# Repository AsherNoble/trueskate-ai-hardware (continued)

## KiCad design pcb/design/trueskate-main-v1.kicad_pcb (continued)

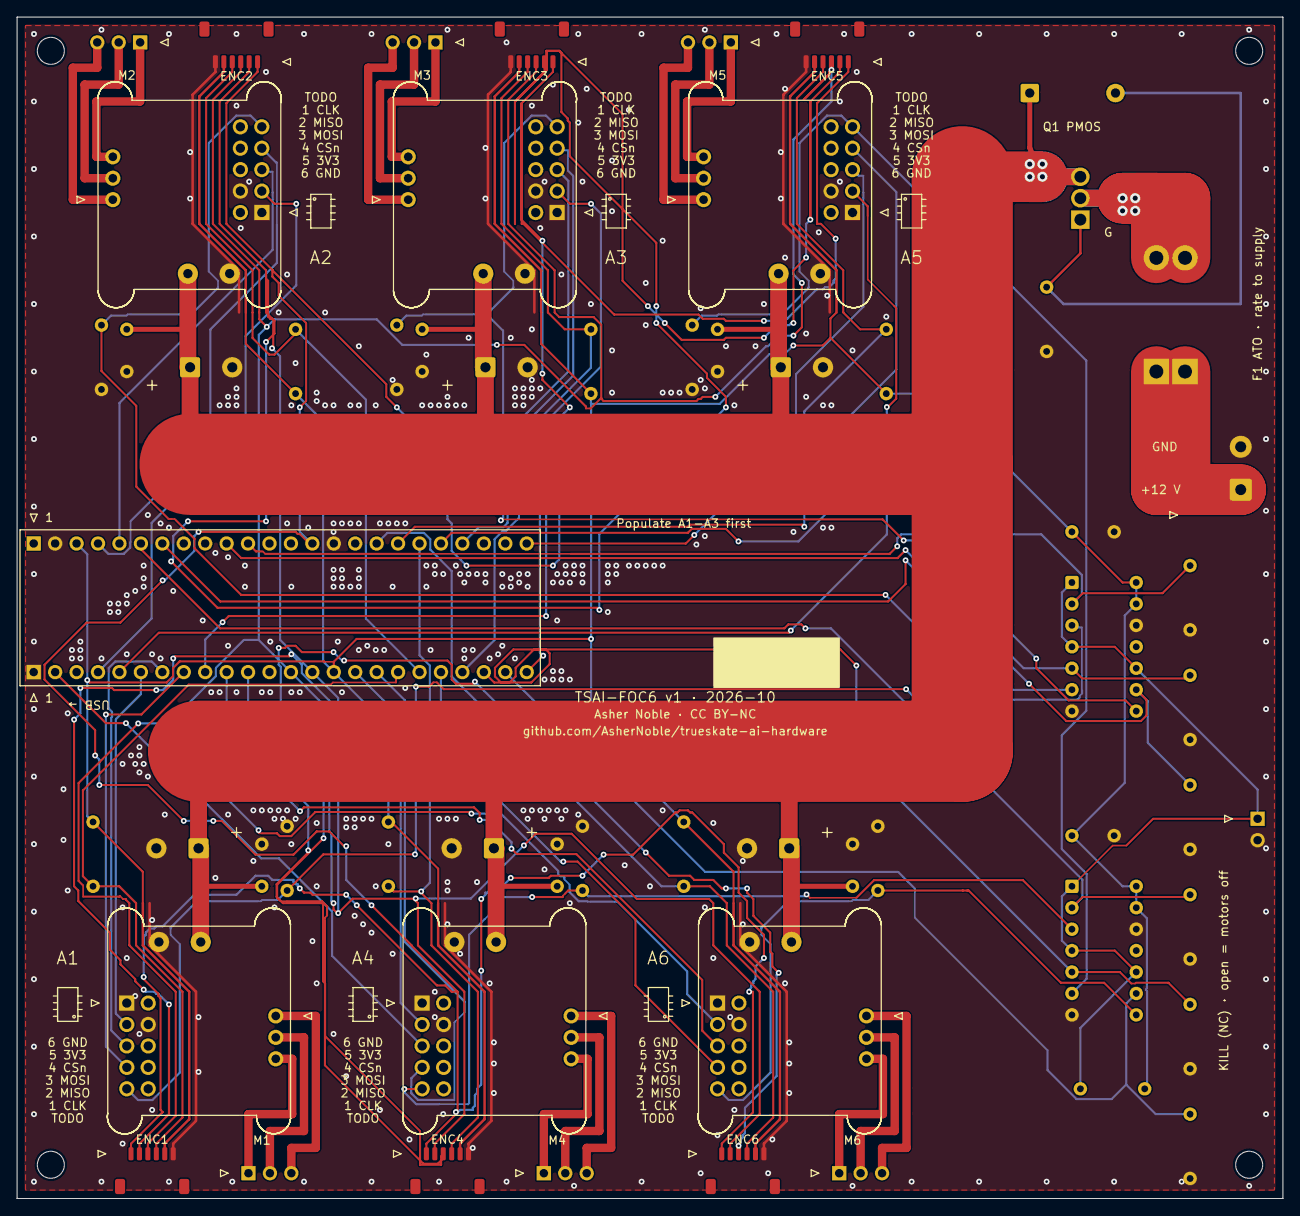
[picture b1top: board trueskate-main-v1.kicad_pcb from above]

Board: 2 copper layers, 150.0 x 140.0 mm, 65 parts (0 on the bottom side), 64 nets.

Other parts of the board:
H1, H2, H3, H4: MountingHole_3.2mm_M3

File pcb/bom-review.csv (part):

Reference,Quantity,Value,Footprint,LCSC,Assembly,Estimated USD each,Notes
J1,1,Teensy 4.1 FEMALE 1x24,TrueSkate:Edge_PinSocket_1x24_P2.54mm_Vertical,,Hand,1.5,"Physical pin legend: GND,0,1,2,3,4,5,6,7,8,9,10,11,12,3V3,24,25,26,27,28,29,30,31,32"
J2,1,Teensy 4.1 FEMALE 1x24,TrueSkate:Edge_PinSocket_1x24_P2.54mm_Vertical,,Hand,1.5,"Physical pin legend: VIN,GND,3V3,23,22,21,20,19,18,17,16,15,14,13,GND,41,40,39,38,37,36,35,34,33"
J11,1,Mini v1.0 / 15-hole socket,TrueSkate:SimpleFOC_Mini_v1.0,,Hand,0.7,Optional axis; female 2x5 + female 1x3 + two >=3A single receptacles; matched mating height
J21,1,MOTOR PHASES male 1x3,TrueSkate:Edge_PinHeader_1x03_P2.54mm_Vertical,,Hand,0.1,Optional axis; outward cable clearance at front edge
J31,1,SM06B-SRSS-TB,TrueSkate:Edge_JST_SH_SM06B-SRSS-TB_1x06-1MP_P1.00mm_Horizontal,C7588156,JLCPCB,0.5,Optional axis; side entry opens toward front (-Y); SH harness pin order UNVERIFIED
R21,1,10k EN pull-down,TrueSkate:Edge_R_Axial_DIN0207_L6.3mm_D2.5mm_P7.62mm_Horizontal,,Hand,0.05,"Optional axis; fit with Mini; 10k, 5% or better"
R31,1,10k CS pull-up,TrueSkate:Edge_R_Axial_DIN0207_L6.3mm_D2.5mm_P7.62mm_Horizontal,,Hand,0.05,"Optional axis; fit with encoder; 10k, 5% or better"
C11,1,1000uF 35V EEUFR1V102B,TrueSkate:Edge_CP_Radial_D12.5mm_P5.00mm,C128476,Hand / owned,0,Optional axis; owned Panasonic diameter12.5mm height20mm pitch5mm
C21,1,100nF 50V ceramic,TrueSkate:Edge_C_Disc_D5.0mm_W2.5mm_P5.00mm,C2979769,Hand,0.13,Optional axis; Vishay K104K10X7RF5UH5
J12,1,Mini v1.0 / 15-hole socket,TrueSkate:SimpleFOC_Mini_v1.0,,Hand,0.7,Optional axis; female 2x5 + female 1x3 + two >=3A single receptacles; matched mating height
J22,1,MOTOR PHASES male 1x3,TrueSkate:Edge_PinHeader_1x03_P2.54mm_Vertical,,Hand,0.1,Optional axis; outward cable clearance at front edge
J32,1,SM06B-SRSS-TB,TrueSkate:Edge_JST_SH_SM06B-SRSS-TB_1x06-1MP_P1.00mm_Horizontal,C7588156,JLCPCB,0.5,Optional axis; side entry opens toward front (-Y); SH harness pin order UNVERIFIED
R22,1,10k EN pull-down,TrueSkate:Edge_R_Axial_DIN0207_L6.3mm_D2.5mm_P7.62mm_Horizontal,,Hand,0.05,"Optional axis; fit with Mini; 10k, 5% or better"
R32,1,10k CS pull-up,TrueSkate:Edge_R_Axial_DIN0207_L6.3mm_D2.5mm_P7.62mm_Horizontal,,Hand,0.05,"Optional axis; fit with encoder; 10k, 5% or better"
C12,1,1000uF 35V EEUFR1V102B,TrueSkate:Edge_CP_Radial_D12.5mm_P5.00mm,C128476,Hand / owned,0,Optional axis; owned Panasonic diameter12.5mm height20mm pitch5mm
C22,1,100nF 50V ceramic,TrueSkate:Edge_C_Disc_D5.0mm_W2.5mm_P5.00mm,C2979769,Hand,0.13,Optional axis; Vishay K104K10X7RF5UH5
J13,1,Mini v1.0 / 15-hole socket,TrueSkate:SimpleFOC_Mini_v1.0,,Hand,0.7,Optional axis; female 2x5 + female 1x3 + two >=3A single receptacles; matched mating height
J23,1,MOTOR PHASES male 1x3,TrueSkate:Edge_PinHeader_1x03_P2.54mm_Vertical,,Hand,0.1,Optional axis; outward cable clearance at front edge
J33,1,SM06B-SRSS-TB,TrueSkate:Edge_JST_SH_SM06B-SRSS-TB_1x06-1MP_P1.00mm_Horizontal,C7588156,JLCPCB,0.5,Optional axis; side entry opens toward front (-Y); SH harness pin order UNVERIFIED
R23,1,10k EN pull-down,TrueSkate:Edge_R_Axial_DIN0207_L6.3mm_D2.5mm_P7.62mm_Horizontal,,Hand,0.05,"Optional axis; fit with Mini; 10k, 5% or better"
R33,1,10k CS pull-up,TrueSkate:Edge_R_Axial_DIN0207_L6.3mm_D2.5mm_P7.62mm_Horizontal,,Hand,0.05,"Optional axis; fit with encoder; 10k, 5% or better"
C13,1,1000uF 35V EEUFR1V102B,TrueSkate:Edge_CP_Radial_D12.5mm_P5.00mm,C128476,Hand / owned,0,Optional axis; owned Panasonic diameter12.5mm height20mm pitch5mm
C23,1,100nF 50V ceramic,TrueSkate:Edge_C_Disc_D5.0mm_W2.5mm_P5.00mm,C2979769,Hand,0.13,Optional axis; Vishay K104K10X7RF5UH5
J14,1,Mini v1.0 / 15-hole socket,TrueSkate:SimpleFOC_Mini_v1.0,,Hand,0.7,Optional axis; female 2x5 + female 1x3 + two >=3A single receptacles; matched mating height
J24,1,MOTOR PHASES male 1x3,TrueSkate:Edge_PinHeader_1x03_P2.54mm_Vertical,,Hand,0.1,Optional axis; outward cable clearance at front edge
J34,1,SM06B-SRSS-TB,TrueSkate:Edge_JST_SH_SM06B-SRSS-TB_1x06-1MP_P1.00mm_Horizontal,C7588156,JLCPCB,0.5,Optional axis; side entry opens toward front (-Y); SH harness pin order UNVERIFIED
R24,1,10k EN pull-down,TrueSkate:Edge_R_Axial_DIN0207_L6.3mm_D2.5mm_P7.62mm_Horizontal,,Hand,0.05,"Optional axis; fit with Mini; 10k, 5% or better"
R34,1,10k CS pull-up,TrueSkate:Edge_R_Axial_DIN0207_L6.3mm_D2.5mm_P7.62mm_Horizontal,,Hand,0.05,"Optional axis; fit with encoder; 10k, 5% or better"
C14,1,1000uF 35V EEUFR1V102B,TrueSkate:Edge_CP_Radial_D12.5mm_P5.00mm,C128476,Hand / owned,0,Optional axis; owned Panasonic diameter12.5mm height20mm pitch5mm
C24,1,100nF 50V ceramic,TrueSkate:Edge_C_Disc_D5.0mm_W2.5mm_P5.00mm,C2979769,Hand,0.13,Optional axis; Vishay K104K10X7RF5UH5
J15,1,Mini v1.0 / 15-hole socket,TrueSkate:SimpleFOC_Mini_v1.0,,Hand,0.7,Optional axis; female 2x5 + female 1x3 + two >=3A single receptacles; matched mating height
J25,1,MOTOR PHASES male 1x3,TrueSkate:Edge_PinHeader_1x03_P2.54mm_Vertical,,Hand,0.1,Optional axis; outward cable clearance at front edge
J35,1,SM06B-SRSS-TB,TrueSkate:Edge_JST_SH_SM06B-SRSS-TB_1x06-1MP_P1.00mm_Horizontal,C7588156,JLCPCB,0.5,Optional axis; side entry opens toward front (-Y); SH harness pin order UNVERIFIED
R25,1,10k EN pull-down,TrueSkate:Edge_R_Axial_DIN0207_L6.3mm_D2.5mm_P7.62mm_Horizontal,,Hand,0.05,"Optional axis; fit with Mini; 10k, 5% or better"
R35,1,10k CS pull-up,TrueSkate:Edge_R_Axial_DIN0207_L6.3mm_D2.5mm_P7.62mm_Horizontal,,Hand,0.05,"Optional axis; fit with encoder; 10k, 5% or better"
C15,1,1000uF 35V EEUFR1V102B,TrueSkate:Edge_CP_Radial_D12.5mm_P5.00mm,C128476,Hand / owned,0,Optional axis; owned Panasonic diameter12.5mm height20mm pitch5mm
C25,1,100nF 50V ceramic,TrueSkate:Edge_C_Disc_D5.0mm_W2.5mm_P5.00mm,C2979769,Hand,0.13,Optional axis; Vishay K104K10X7RF5UH5
J16,1,Mini v1.0 / 15-hole socket,TrueSkate:SimpleFOC_Mini_v1.0,,Hand,0.7,Optional axis; female 2x5 + female 1x3 + two >=3A single receptacles; matched mating height
J26,1,MOTOR PHASES male 1x3,TrueSkate:Edge_PinHeader_1x03_P2.54mm_Vertical,,Hand,0.1,Optional axis; outward cable clearance at front edge
J36,1,SM06B-SRSS-TB,TrueSkate:Edge_JST_SH_SM06B-SRSS-TB_1x06-1MP_P1.00mm_Horizontal,C7588156,JLCPCB,0.5,Optional axis; side entry opens toward front (-Y); SH harness pin order UNVERIFIED
R26,1,10k EN pull-down,TrueSkate:Edge_R_Axial_DIN0207_L6.3mm_D2.5mm_P7.62mm_Horizontal,,Hand,0.05,"Optional axis; fit with Mini; 10k, 5% or better"
R36,1,10k CS pull-up,TrueSkate:Edge_R_Axial_DIN0207_L6.3mm_D2.5mm_P7.62mm_Horizontal,,Hand,0.05,"Optional axis; fit with encoder; 10k, 5% or better"
C16,1,1000uF 35V EEUFR1V102B,TrueSkate:Edge_CP_Radial_D12.5mm_P5.00mm,C128476,Hand / owned,0,Optional axis; owned Panasonic diameter12.5mm height20mm pitch5mm
C26,1,100nF 50V ceramic,TrueSkate:Edge_C_Disc_D5.0mm_W2.5mm_P5.00mm,C2979769,Hand,0.13,Optional axis; Vishay K104K10X7RF5UH5
J5,1,12V INPUT + / -,"TrueSkate:Edge_TerminalBlock_Phoenix_MKDS-1,5-2-5.08_1x02_P5.08mm_Horizontal",,Hand,2,Phoenix1715721 17.5A nominal; verify wire size and applicable rating
F1,1,Keystone 3557-2 ATO holder,TrueSkate:Keystone_3557-2_ATO,C352820,Hand,1.68,One complete holder includes both contacts for one standard ATO fuse; fuse purchased separately
J6,1,NC KILL SWITCH,TrueSkate:Edge_PinHeader_1x02_P2.54mm_Vertical,,Hand,0.1,Open loop disables every Mini; closed loop permits firmware EN
R1,1,10k /OE pull-up,TrueSkate:Edge_R_Axial_DIN0207_L6.3mm_D2.5mm_P7.62mm_Horizontal,,Hand,0.05,"; 10k, 5% or better"
U1,1,SN74LV125AN,TrueSkate:Edge_DIP-14_W7.62mm,,Hand,1,"Shared mandatory kill buffer; pins1/4/10=/OE,13 disabled; TI SCES124O"
C1,1,100nF buffer bypass,TrueSkate:Edge_C_Disc_D5.0mm_W2.5mm_P5.00mm,,Hand,0.13,
R41,1,10k EN command pull-down,TrueSkate:Edge_R_Axial_DIN0207_L6.3mm_D2.5mm_P7.62mm_Horizontal,,Hand,0.05,"Shared buffer input bias; may omit with corresponding axis; 10k, 5% or better"
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
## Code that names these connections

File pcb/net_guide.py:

#!/usr/bin/env python3
"""One-page beginner net guide; checks that every real carrier net is covered."""
import json
from pathlib import Path
from xml.sax.saxutils import escape
from reportlab.lib import colors
from reportlab.lib.enums import TA_LEFT
from reportlab.lib.pagesizes import A4
from reportlab.lib.styles import ParagraphStyle
from reportlab.platypus import SimpleDocTemplate, Paragraph, Spacer, Table, TableStyle
from pypdf import PdfReader

ROOT=Path(__file__).resolve().parent
DOCS=ROOT.parent/'docs/pcb'
groups=[
(['12V_IN'],'J5 positive to F1 input, before the fuse. Original outer-layer input route; correct polarity required.'),
(['12V_FUSED'],'F1 output to all Mini VIN contacts and local capacitors. Original outer-layer bus and feeds; 1 oz copper.'),
(['3V3'],'Teensy regulator to encoders, CS pull-ups, kill buffers and /OE pull-up. USB powers the Teensy.'),
(['GND'],'Stitched top/bottom GND fills join supply negative, logic, Minis and capacitor returns. No isolation.'),
(['SPI_SCK'],'Teensy 13 to all encoders. SH contact assignment is provisional; see README verification table.'),
(['SPI_MOSI'],'Teensy 11 to all encoders. Host-to-encoder data.'),
(['SPI_MISO'],'Encoders to Teensy 12. Only the selected encoder may drive this shared line.'),
([f'A{i}_PWM{p}' for i in range(1,7) for p in range(1,4)],'Three logic PWM instructions per axis from Teensy to Mini. Existing pin map retained.'),
([f'A{i}_EN_CMD' for i in range(1,7)],'Teensy EN command to a buffer input; 10k input pull-down holds an undriven command low.'),
(['EN_DISABLE'],'J6 NC loop shorts this net to GND to permit commands. Open loop lets R1 pull it high and disable all buffers.'),
([f'A{i}_EN' for i in range(1,7)],'Buffered enable to Mini pin9. Open kill loop makes buffer high impedance; local 10k pulls EN low.'),
([f'A{i}_CS' for i in range(1,7)],'Individual active-low encoder select with 10k pull-up. Fit with its encoder; deselect all before SPI.'),
([f'A{i}_PH{p}' for i in range(1,7) for p in range(1,4)],'Mini P3/P2/P1 to male motor header1/2/3. Never move phase cables with 12V live.')
]
actual={n for p in json.loads((ROOT/'circuit.json').read_text()) for n in p['nets'] if n}
covered=[n for ns,_ in groups for n in ns]
assert len(covered)==len(set(covered)) and set(covered)==actual
axes=json.loads((ROOT/'design.json').read_text())['axes']
title='TrueSkate v1 - every net, in plain English'
intro=('Identical labels are one electrical net. Shared copper remains continuous with any axis unpopulated. '
       'The two shared kill buffers and their bias/bypass parts remain fitted. Plug-in modules perform motor control.')
labels=['12V_IN','12V_FUSED','3V3','GND','SPI_SCK','SPI_MOSI','SPI_MISO',
        'A<n>_PWM<p>','A<n>_EN_CMD','EN_DISABLE','A<n>_EN','A<n>_CS','A<n>_PH<p>']
footer=('SH pin-to-net order is UNVERIFIED: see README and check the actual AS5048A board with a multimeter. '
        'Opening kill disables EN but does not disconnect 12V; reclosing permits the current command without a latch. '
        'Human review, mechanical fit, startup and noise tests remain required before manufacture.')
md='# '+title+'\n\n'+intro+'\n\n| Net or repeated family | What it connects and why |\n|---|---|\n'
for label,(_,desc) in zip(labels,groups): md+='| `'+label+'` | '+desc+' |\n'
md+='\nNames expand literally: for example `A2_PWM3` and `A6_PH1`. This covers every name, not just a sample.\n\n'
md+='| Axis | Movement | Teensy PWM1/2/3 | Teensy EN | Teensy CS |\n|---|---|---|---|---|\n'
for i,a in enumerate(axes,1):md+=f"| A{i} | {a['name'].replace('_',' ')} | {' / '.join(map(str,a['pwm']))} | {a['enable']} | {a['cs']} |\n"
md+='\n'+footer+'\n'
(DOCS/'nets.md').write_text(md)
body=ParagraphStyle('body',fontName='Helvetica',fontSize=8.7,leading=11.1,textColor=colors.HexColor('#172634'),spaceAfter=3)
head=ParagraphStyle('head',parent=body,fontName='Helvetica-Bold',fontSize=16,leading=19,spaceAfter=7)
small=ParagraphStyle('small',parent=body,fontSize=8,leading=10)
cell=ParagraphStyle('cell',parent=body,fontSize=8.3,leading=10.5,spaceAfter=0)
net=ParagraphStyle('net',parent=cell,fontName='Courier-Bold',fontSize=8.0)
story=[Paragraph(title,head),Paragraph(escape(intro),body),Spacer(1,5)]
rows=[[Paragraph('NET / FAMILY',cell),Paragraph('CONNECTION AND PURPOSE',cell)]]
for label,(_,desc) in zip(labels,groups): rows.append([Paragraph(escape(label),net),Paragraph(escape(desc),cell)])
t=Table(rows,colWidths=[136,395],hAlign='LEFT')
t.setStyle(TableStyle([('VALIGN',(0,0),(-1,-1),'TOP'),('BACKGROUND',(0,0),(-1,0),colors.HexColor('#e7eef5')),
                      ('LINEBELOW',(0,0),(-1,0),.5,colors.HexColor('#829bb3')),
                      ('LINEBELOW',(0,1),(-1,-1),.25,colors.HexColor('#d9e1e8')),
                      ('LEFTPADDING',(0,0),(-1,-1),5),('RIGHTPADDING',(0,0),(-1,-1),5),
                      ('TOPPADDING',(0,0),(-1,-1),4),('BOTTOMPADDING',(0,0),(-1,-1),4)]))
story+=[t,Spacer(1,7),Paragraph('TEENSY PIN NUMBERS (not socket contact numbers)',small)]
mapping=[['AXIS / MOVEMENT','PWM1 / PWM2 / PWM3','EN','CSn']]
for i,a in enumerate(axes,1):mapping.append([f"A{i} / {a['name'].replace('_',' ')}",' / '.join(map(str,a['pwm'])),str(a['enable']),str(a['cs'])])
t=Table(mapping,colWidths=[236,155,70,70],hAlign='LEFT')
t.setStyle(TableStyle([('FONTNAME',(0,0),(-1,0),'Helvetica-Bold'),('FONTNAME',(0,1),(-1,-1),'Helvetica'),('FONTSIZE',(0,0),(-1,-1),8.2),
                      ('BACKGROUND',(0,0),(-1,0),colors.HexColor('#e7eef5')),('TOPPADDING',(0,0),(-1,-1),3),('BOTTOMPADDING',(0,0),(-1,-1),3)]))
story += [t,Spacer(1,7),Paragraph(escape(footer),small)]
pdf=ROOT/'net-guide-review.pdf'
doc=SimpleDocTemplate(str(pdf),pagesize=A4,rightMargin=32,leftMargin=32,topMargin=25,bottomMargin=25,
                      title=title,author='TrueSkate hardware review')
doc.build(story)
assert len(PdfReader(pdf).pages)==1,'Net guide must remain one page'
print(f'Wrote one-page net guide; all {len(actual)} real net names covered exactly once by the families.')
